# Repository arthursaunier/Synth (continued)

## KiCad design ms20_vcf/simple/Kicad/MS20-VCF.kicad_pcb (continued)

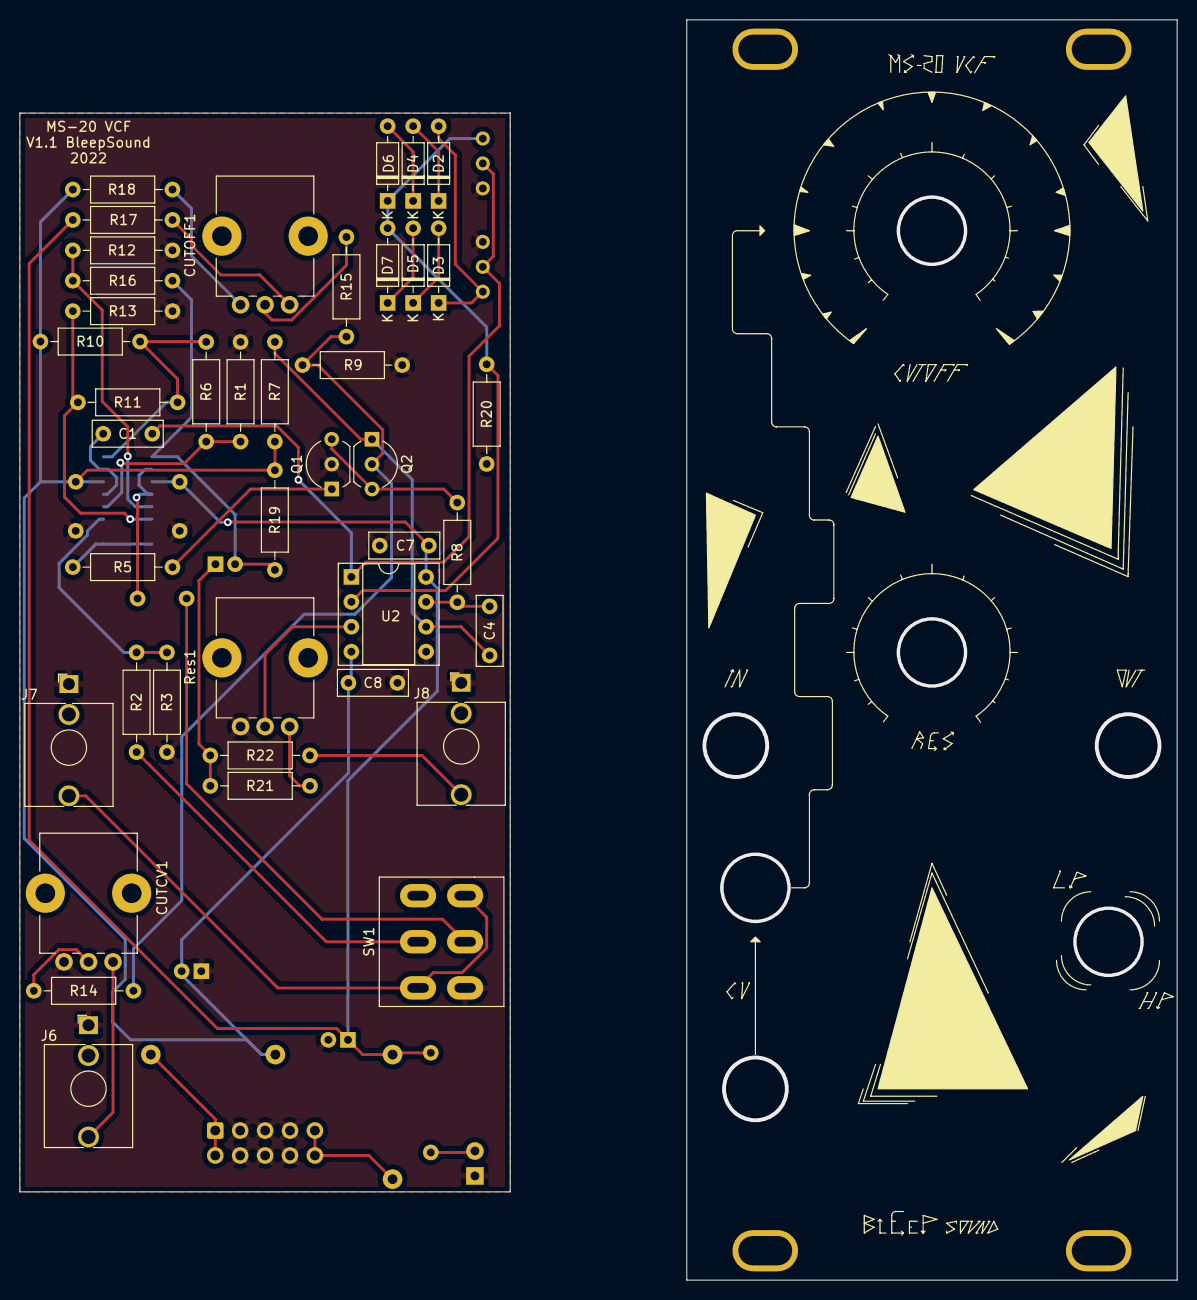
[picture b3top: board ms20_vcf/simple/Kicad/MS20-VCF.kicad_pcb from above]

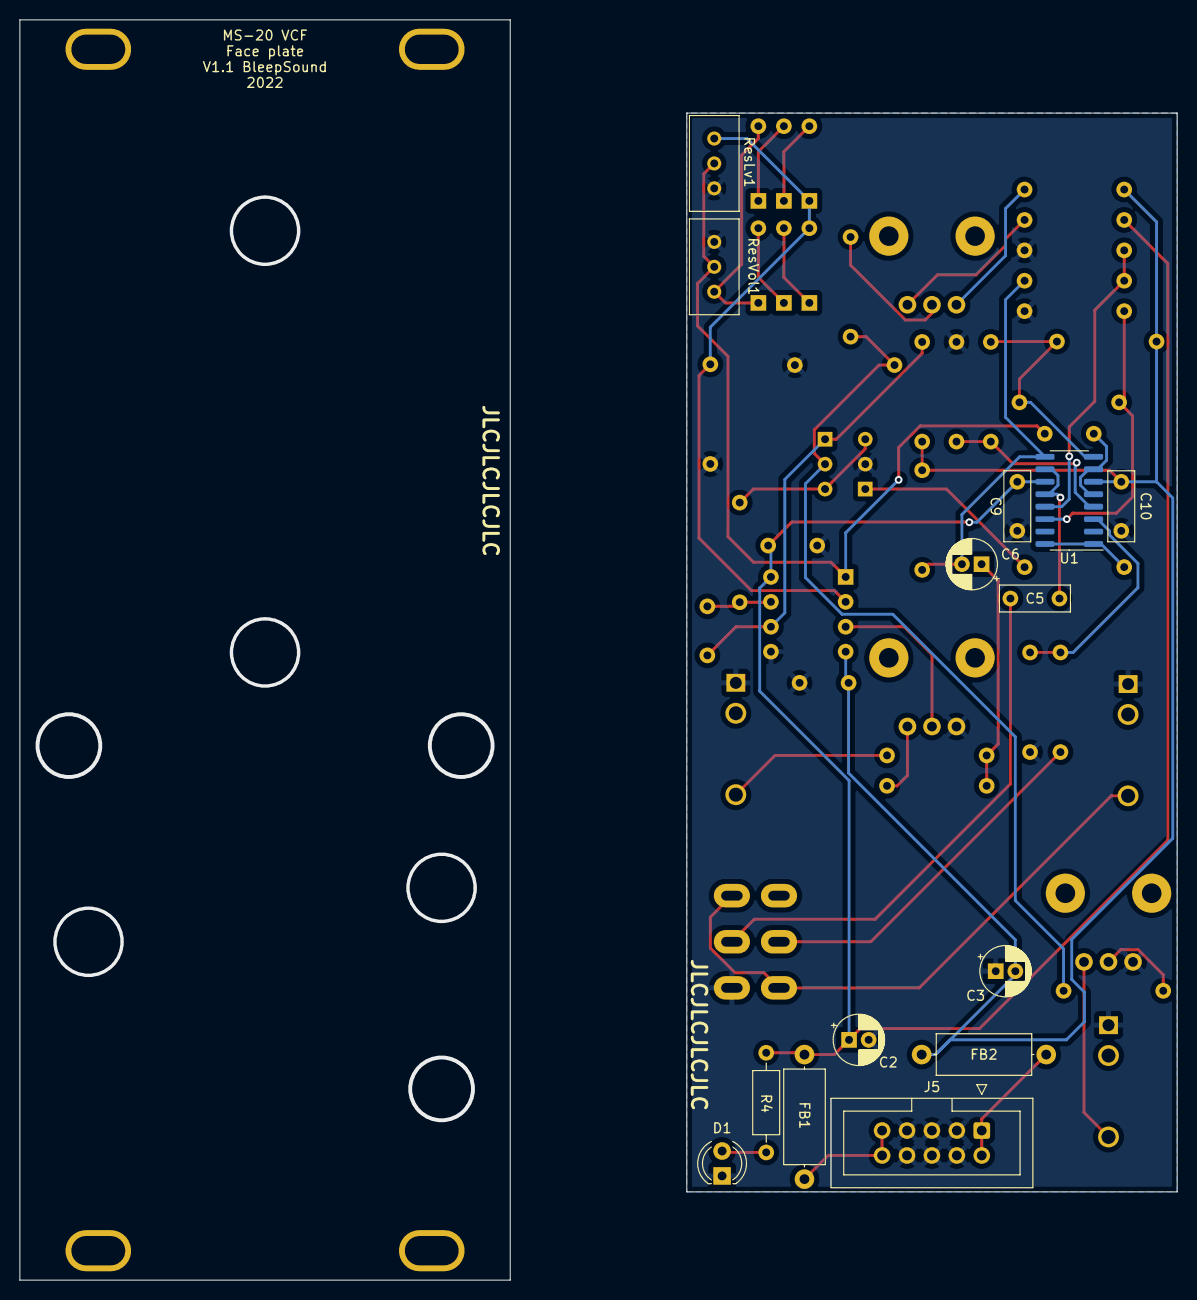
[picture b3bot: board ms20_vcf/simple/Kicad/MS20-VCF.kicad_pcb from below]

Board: 2 copper layers, 118.0 x 128.5 mm, 59 parts (14 on the bottom side), 39 nets.

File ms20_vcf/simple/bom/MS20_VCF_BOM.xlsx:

References | Quantity | Value | Footprint | Specs | Link | Price/100 | Price
C7, C8, C9, C10 | 4 | 100nF | C_Disc_D7.0mm_W2.5mm_P5.00mm | 100nF, 50V, ceramic disc | https://www.taydaelectronics.com/capacitors/ceramic-disc-cap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 | 0.01 | 0.04
C1, C4, C5 | 3 | 1nF | C_Disc_D7.0mm_W2.5mm_P5.00mm | 1nF, 50V, ceramic disc | https://www.taydaelectronics.com/capacitors/ceramic-disc-cap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 | 0.01 | 0.03
C2, C3, C6 | 3 | 10µ | CP_Radial_D5.0mm_P2.00mm | 10µF, 50V | https://www.taydaelectronics.com/capacitors/electrolytic-cap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 | 0.02 | 0.06
FB1, FB2 | 2 | 10R | L_Axial_L9.5mm_D4.0mm_P12.70mm_Horizontal_Fastron_SMCC |  | https://www.taydaelectronics.com/axial-ferrite-bead-76-ohm.html | 0.08 | 0.16
R2, R6, R7, R11, R15, R16 | 6 | 100k | R_Axial_DIN0207_L6.3mm_D2.5mm_P10.16mm_Horizontal | 1/4W metal film 1% resistor | https://www.taydaelectronics.com/resistors/1-4w-metal-film-r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 | 1.4999999999999999E-2 | 0.09
R1, R3, R12, R13 | 4 | 470R | R_Axial_DIN0207_L6.3mm_D2.5mm_P10.16mm_Horizontal | 1/4W metal film 1% resistor | https://www.taydaelectronics.com/resistors/1-4w-metal-film-r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 | 1.4999999999999999E-2 | 0.06
R4, R5, R9, R20 | 4 | 2.2k | R_Axial_DIN0207_L6.3mm_D2.5mm_P10.16mm_Horizontal | 1/4W metal film 1% resistor | https://www.taydaelectronics.com/resistors/1-4w-metal-film-r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 | 1.4999999999999999E-2 | 0.06
R8, R21, R22 | 3 | 1k | R_Axial_DIN0207_L6.3mm_D2.5mm_P10.16mm_Horizontal | 1/4W metal film 1% resistor | https://www.taydaelectronics.com/resistors/1-4w-metal-film-r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 | 1.4999999999999999E-2 | 4.4999999999999998E-2
R10, R19 | 2 | 1.8k | R_Axial_DIN0207_L6.3mm_D2.5mm_P10.16mm_Horizontal | 1/4W metal film 1% resistor | https://www.taydaelectronics.com/resistors/1-4w-metal-film-r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 | 1.4999999999999999E-2 | 0.03
R14 | 1 | 82k | R_Axial_DIN0207_L6.3mm_D2.5mm_P10.16mm_Horizontal | 1/4W metal film 1% resistor | https://www.taydaelectronics.com/resistors/1-4w-metal-film-r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 | 1.4999999999999999E-2 | 1.4999999999999999E-2
R17 | 1 | 33k | R_Axial_DIN0207_L6.3mm_D2.5mm_P10.16mm_Horizontal | 1/4W metal film 1% resistor | https://www.taydaelectronics.com/resistors/1-4w-metal-film-r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 | 1.4999999999999999E-2 | 1.4999999999999999E-2
R18 | 1 | 56k | R_Axial_DIN0207_L6.3mm_D2.5mm_P10.16mm_Horizontal | 1/4W metal film 1% resistor | https://www.taydaelectronics.com/resistors/1-4w-metal-film-r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 | 1.4999999999999999E-2 | 1.4999999999999999E-2
D2, D3, D4, D5, D6, D7 | 6 | 1N4148 | D_DO-35_SOD27_P7.62mm_Horizontal | 1N4148 diode | https://www.taydaelectronics.com/1n4148-switching-signal-diode.html | 0.01 | 0.06
D1 | 1 | LED-12V | LED_D4.0mm |  | https://www.taydaelectronics.com/leds/round-leds/5mm-leds.html | 0.03 | 0.03
U1 | 1 | LM13700 | SOIC-16_3.9x9.9mm_P1.27mm | OTA | https://www.taydaelectronics.com/lm13700-lm13700n-operationa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 | 3.99 | 1.99
U2 | 2 | TL072 | DIP-8_W7.62mm_Socket | OpAmp | https://www.taydaelectronics.com/tl072-low-noise-j-fet-dual-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 | 1.99 | 3.98
SW1 | 1 | Hpass/Lpass Switch | SW_DPDT_Toggle |  | https://www.taydaelectronics.com/mini-toggle-switch-dpdt-on-on.html | 0.59 | 0.59
CUTCV1, CUTOFF1, Res1 | 3 | 100k | Potentiometer_Bourns_PTV09A-1_Single_Vertical |  | https://www.mouser.fr/ProductDetail/652-PTV09A4025FB104 | 0.84699999999999998 | 2.5409999999999999
ResLv1 | 1 | 3.3k | Potentiometer_Bourns_3386C_Horizontal |  | https://www.taydaelectronics.com/10k-ohm-trimmer-potentiomet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 | 0.28000000000000003 | 0.28000000000000003
ResVol1 | 1 | 10k | Potentiometer_Bourns_3386C_Horizontal |  | https://www.taydaelectronics.com/10k-ohm-trimmer-potentiomet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 | 0.28000000000000003 | 0.28000000000000003
Q1, Q2 | 2 | BC559 | TO-92_Inline |  | https://www.taydaelectronics.com/bc559bta-bc559b-bc559-trans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 | 0.08 | 0.16
J5 | 1 | Power Input | IDC-Header_2x05_P2.54mm_Vertical |  | https://www.taydaelectronics.com/10-pin-box-header-connector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 | 0.15 | 0.15
J6, J7, J8 | 3 |  | Jack_3.5mm_QingPu_WQP-PJ398SM_Vertical_CircularHoles | 3,5mm mono Jack socket | https://www.thonk.co.uk/shop/3-5mm-jacks/ | 0.32 | 0.96
 |  |  |  |  |  | Total | 11.600999999999999

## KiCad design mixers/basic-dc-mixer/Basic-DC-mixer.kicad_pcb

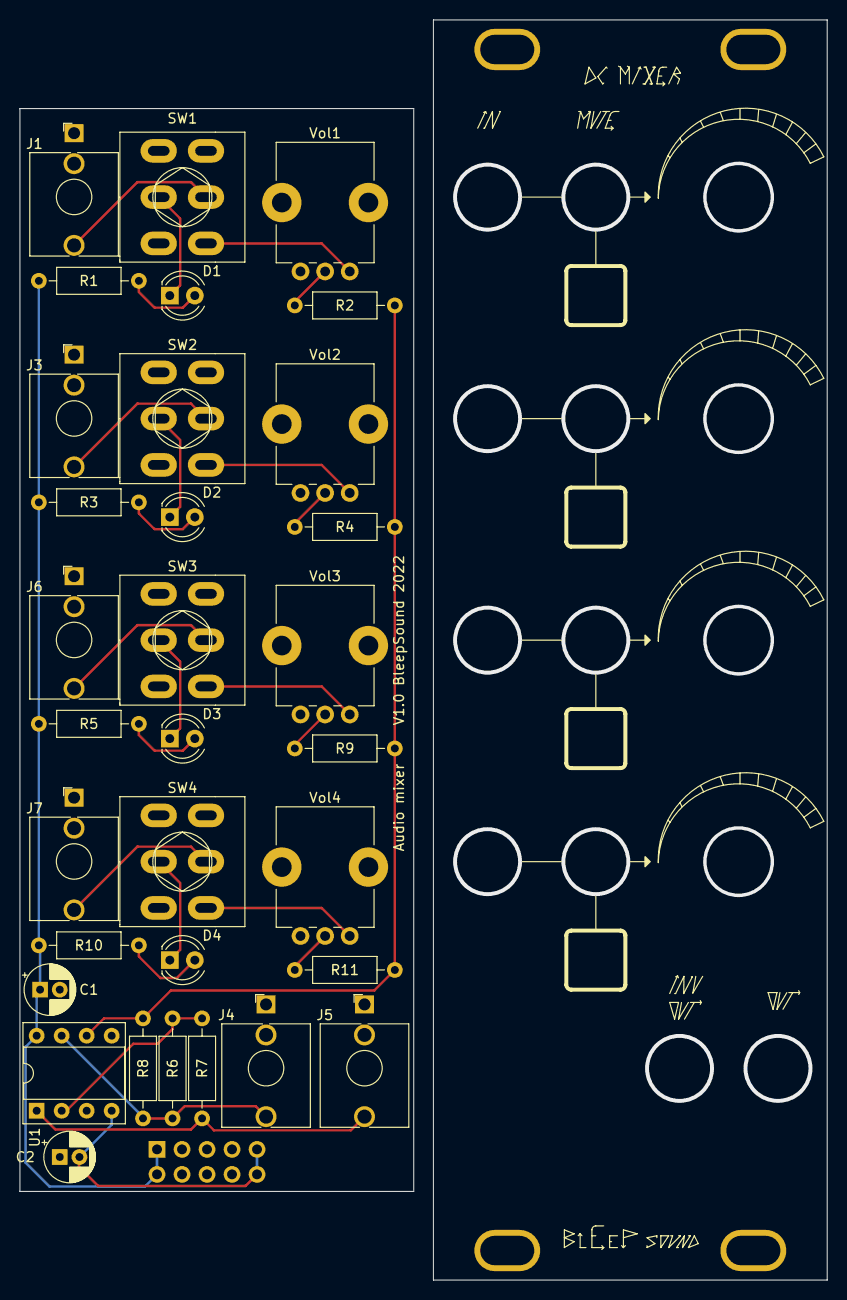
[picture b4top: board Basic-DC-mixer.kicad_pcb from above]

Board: 2 copper layers, 82.0 x 128.0 mm, 37 parts (1 on the bottom side), 27 nets.

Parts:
C1, C2: 10µ; CP_Radial_D5.0mm_P2.00mm
D1, D2, D3, D4: LED-mute; LED_D4.0mm
H1, H2, H3, H4: MountingHole; Doepfer Mounting hole
J1, J3, J6, J7: In; Thonkiconn
J2: Power Input; PinHeader_2x05_P2.54mm_Vertical
J4: InvOut; Thonkiconn
J5: Out; Thonkiconn
R1, R3, R5, R10: 4.7k; R_Axial_DIN0207_L6.3mm_D2.5mm_P10.16mm_Horizontal
R2, R4, R8, R9, R11: 100k; R_Axial_DIN0207_L6.3mm_D2.5mm_P10.16mm_Horizontal
R6, R7: 10k; R_Axial_DIN0207_L6.3mm_D2.5mm_P10.16mm_Horizontal
SW1, SW2, SW3, SW4: Mute; SW_DPDT_Toggle
U1: TL072; DIP-8_W7.62mm_Socket
Vol1, Vol2, Vol3, Vol4: 10k; Pot-bourns-alpha

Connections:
+12V: C1.1, J2.1, J2.2, R1.1, R3.1, R5.1, R10.1, U1.8 (V+)
-12V: C2.2, J2.9, J2.10, U1.4 (V-)
GND: C1.2, C2.1, J1.S, J2.3, J2.4, J2.5, J2.6, J2.7, J2.8, J3.S, J4.S, J5.S, J6.S, J7.S, SW1.1 (A), SW2.1 (A), SW3.1 (A), SW4.1 (A), U1.3 (+), U1.5 (+), Vol1.3, Vol2.3, Vol3.3, Vol4.3
unnamed: D1.1 (K), SW1.2 (B)
unnamed: D1.2 (A), R1.2
unnamed: D2.1 (K), SW2.2 (B)
unnamed: D2.2 (A), R3.2
unnamed: D3.1 (K), SW3.2 (B)
unnamed: D3.2 (A), R5.2
unnamed: D4.1 (K), SW4.2 (B)
unnamed: D4.2 (A), R10.2
unnamed: J1.T, SW1.5 (B)
unnamed: J3.T, SW2.5 (B)
unnamed: J4.T, R6.2, R8.1, U1.7
unnamed: J5.T, R7.1, U1.1
unnamed: J6.T, SW3.5 (B)
unnamed: J7.T, SW4.5 (B)
unnamed: R2.2, Vol1.2
unnamed: R4.2, Vol2.2
unnamed: R6.1, R7.2, U1.2 (-)
unnamed: R9.2, Vol3.2
unnamed: R2.1, R4.1, R8.2, R9.1, R11.1, U1.6 (-)
unnamed: R11.2, Vol4.2
unnamed: SW1.6 (C), Vol1.1
unnamed: SW2.6 (C), Vol2.1
unnamed: SW3.6 (C), Vol3.1
unnamed: SW4.6 (C), Vol4.1

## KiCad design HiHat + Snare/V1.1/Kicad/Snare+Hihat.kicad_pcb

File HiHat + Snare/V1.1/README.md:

# Hi-Hat + Snare

## V1.1

2 white noise generators with VCAs to create Hihat or Snare sound. 

Built on the same module, with 2 separate voices (completly independent)

No CV

This version adds boxed IDC headers, minor corrections on components positions and a gain change of the output buffers on each voice.

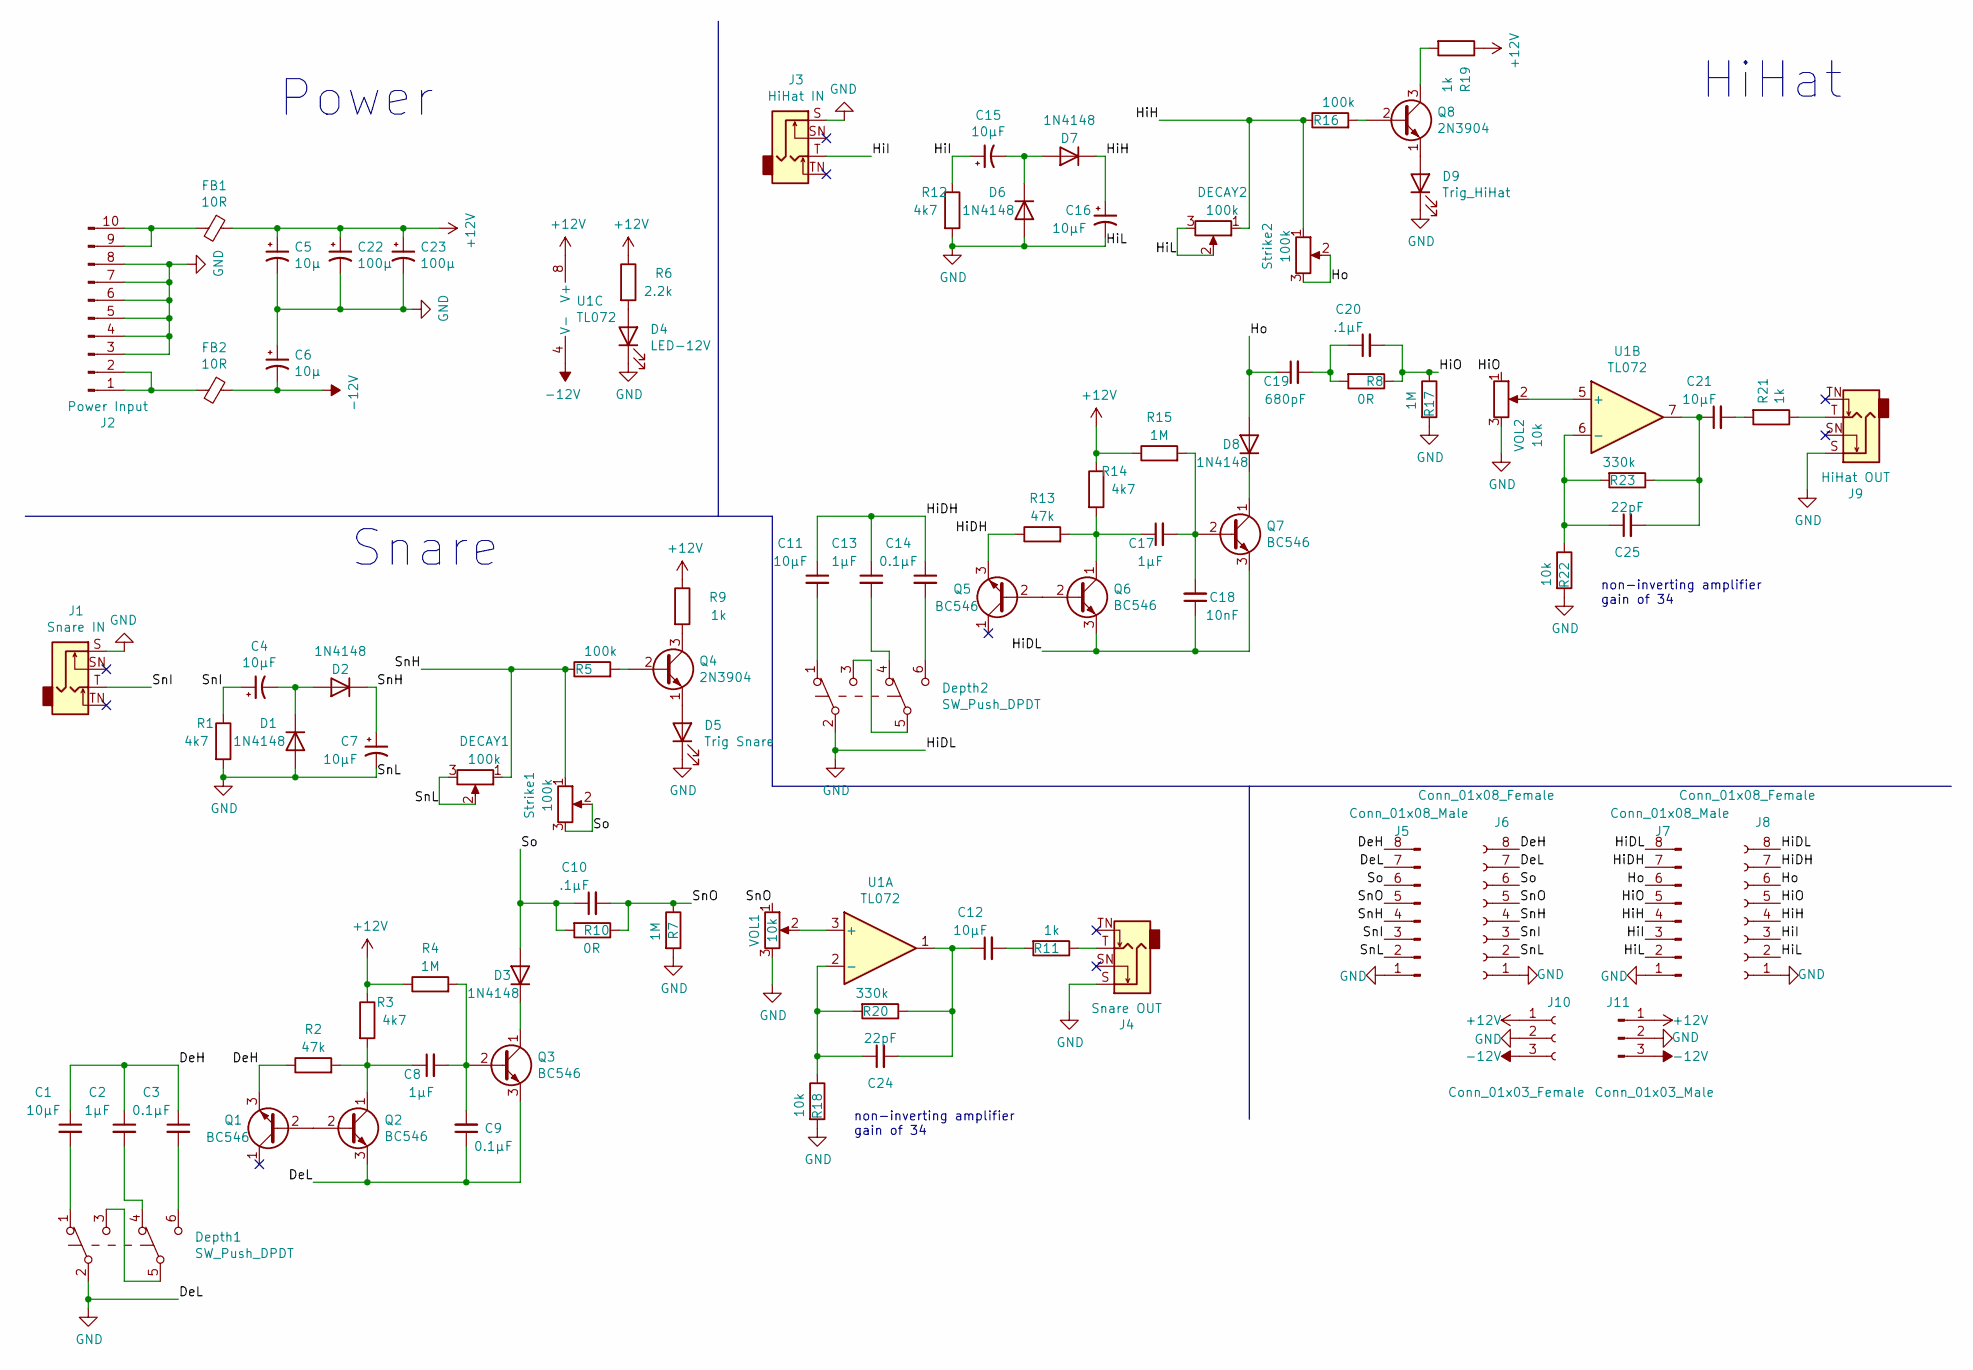
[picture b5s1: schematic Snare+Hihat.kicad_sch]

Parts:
C1, C11, C12, C21: 10µF; C_Disc_D7.0mm_W2.5mm_P5.00mm
C2, C8, C13, C17: 1µF; C_Disc_D7.0mm_W2.5mm_P5.00mm
C3, C9, C14: 0.1µF; C_Disc_D7.0mm_W2.5mm_P5.00mm
C4, C7, C15, C16: 10µF; CP_Radial_D5.0mm_P2.00mm
C5, C6: 10µ; CP_Radial_D5.0mm_P2.00mm
C10, C20: .1µF; C_Disc_D7.0mm_W2.5mm_P5.00mm
C18: 10nF; C_Disc_D7.0mm_W2.5mm_P5.00mm
C19: 680pF; C_Disc_D7.0mm_W2.5mm_P5.00mm
C22, C23: 100µ; CP_Radial_D5.0mm_P2.00mm
C24, C25: 22pF; C_Disc_D7.0mm_W2.5mm_P5.00mm
D1, D2, D3, D6, D7, D8: 1N4148; D_DO-35_SOD27_P7.62mm_Horizontal
D4: LED-12V; LED_D4.0mm
D5: Trig Snare; LED_D4.0mm
D9: Trig_HiHat; LED_D4.0mm
DECAY1, DECAY2: 100k; Pot-bourns-alpha
Depth1, Depth2: SW_Push_DPDT; SW_DPDT_Toggle
FB1, FB2: 10R; L_Axial_L9.5mm_D4.0mm_P12.70mm_Horizontal_Fastron_SMCC
J1: Snare IN; Thonkiconn
J2: Power Input; IDC-Header_2x05_P2.54mm_Vertical
J3: HiHat IN; Thonkiconn
J4: Snare OUT; Thonkiconn
J5, J7: Conn_01x08_Male; PinHeader_1x08_P2.54mm_Vertical
J6, J8: Conn_01x08_Female; PinSocket_1x08_P2.54mm_Vertical
J9: HiHat OUT; Thonkiconn
J10: Conn_01x03_Female; PinSocket_1x03_P2.54mm_Vertical
J11: Conn_01x03_Male; PinHeader_1x03_P2.54mm_Vertical
Q1, Q2, Q3, Q5, Q6, Q7: BC546; TO-92_Inline
Q4, Q8: 2N3904; TO-92_Inline
R1, R3, R12, R14: 4k7; R_Axial_DIN0207_L6.3mm_D2.5mm_P10.16mm_Horizontal
R2, R13: 47k; R_Axial_DIN0207_L6.3mm_D2.5mm_P10.16mm_Horizontal
R4, R7, R15, R17: 1M; R_Axial_DIN0207_L6.3mm_D2.5mm_P10.16mm_Horizontal
R5, R16: 100k; R_Axial_DIN0207_L6.3mm_D2.5mm_P2.54mm_Vertical
R6: 2.2k; R_Axial_DIN0207_L6.3mm_D2.5mm_P10.16mm_Horizontal
R8, R10: 0R; R_Axial_DIN0207_L6.3mm_D2.5mm_P10.16mm_Horizontal
R9, R19: 1k; R_Axial_DIN0207_L6.3mm_D2.5mm_P2.54mm_Vertical
R11, R21: 1k; R_Axial_DIN0207_L6.3mm_D2.5mm_P10.16mm_Horizontal
R18, R22: 10k; R_Axial_DIN0207_L6.3mm_D2.5mm_P2.54mm_Vertical
R20, R23: 330k; R_Axial_DIN0207_L6.3mm_D2.5mm_P2.54mm_Vertical
Strike1, Strike2: 100k; Pot-bourns-alpha
U1: TL072; DIP-8_W7.62mm_Socket
VOL1, VOL2: 10k; Pot-bourns-alpha

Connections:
+12V: C5.1, C22.1, C23.1, FB1.1, J10.1, J11.1, R3.1, R4.1, R6.1, R9.1, R14.1, R15.1, R19.1, U1.8 (V+)
-12V: C6.2, FB2.1, J10.3, J11.3, U1.4 (V-)
/DeH: C1.1, C2.1, C3.1, J5.8, J6.8, Q1.3 (E), R2.1
/HiDH: C11.1, C13.1, C14.1, J7.7, J8.7, Q5.3 (E), R13.1
/HiH: C16.1, D7.1 (K), DECAY2.1, J7.4, J8.4, R16.1, Strike2.1
/HiI: C15.1, J3.T, J7.3, J8.3, R12.1
/HiO: C20.2, J7.5, J8.5, R8.1, R17.1, VOL2.1
/Ho: C19.1, D8.2 (A), J7.6, J8.6, Strike2.2, Strike2.3
/SnH: C7.1, D2.1 (K), DECAY1.1, J5.4, J6.4, R5.1, Strike1.1
/SnI: C4.1, J1.T, J5.3, J6.3, R1.1
/SnO: C10.2, J5.5, J6.5, R7.1, R10.1, VOL1.1
/So: C10.1, D3.2 (A), J5.6, J6.6, R10.2, Strike1.2, Strike1.3
GND: C5.2, C6.1, C7.2, C9.1, C16.2, C18.1, C22.2, C23.2, D1.2 (A), D4.1 (K), D5.1 (K), D6.2 (A), D9.1 (K), DECAY1.2, DECAY1.3, DECAY2.2, DECAY2.3, Depth1.2 (B), Depth2.2 (B), J1.S, J2.3, J2.4, J2.5, J2.6, J2.7, J2.8, J3.S, J4.S, J5.1, J5.2, J5.7, J6.1, J6.2, J6.7, J7.1, J7.2, J7.8, J8.1, J8.2, J8.8, J9.S, J10.2, J11.2, Q2.3 (E), Q3.3 (E), Q6.3 (E), Q7.3 (E), R1.2, R7.2, R12.2, R17.2, R18.2, R22.2, VOL1.3, VOL2.3
unnamed: C1.2, Depth1.1 (A)
unnamed: C2.2, Depth1.4 (A)
unnamed: C3.2, Depth1.6 (C)
unnamed: C4.2, D1.1 (K), D2.2 (A)
unnamed: C8.1, Q2.1 (C), R2.2, R3.2
unnamed: C8.2, C9.2, Q3.2 (B), R4.2
unnamed: C11.2, Depth2.1 (A)
unnamed: C12.1, C24.2, R20.1, U1.1
unnamed: C12.2, R11.2
unnamed: C13.2, Depth2.4 (A)
unnamed: C14.2, Depth2.6 (C)
unnamed: C15.2, D6.1 (K), D7.2 (A)
unnamed: C17.1, Q6.1 (C), R13.2, R14.2
unnamed: C17.2, C18.2, Q7.2 (B), R15.2
unnamed: C19.2, C20.1, R8.2
unnamed: C21.1, C25.2, R23.1, U1.7
unnamed: C21.2, R21.2
unnamed: D3.1 (K), Q3.1 (C)
unnamed: D4.2 (A), R6.2
unnamed: D5.2 (A), Q4.1 (E)
unnamed: D8.1 (K), Q7.1 (C)
unnamed: D9.2 (A), Q8.1 (E)
unnamed: Depth1.3 (C), Depth1.5 (B)
unnamed: Depth2.3 (C), Depth2.5 (B)
unnamed: FB1.2, J2.9, J2.10
unnamed: FB2.2, J2.1, J2.2
unnamed: J4.T, R11.1
unnamed: J9.T, R21.1
unnamed: Q1.2 (B), Q2.2 (B)
unnamed: Q4.2 (B), R5.2
unnamed: Q4.3 (C), R9.2
unnamed: Q5.2 (B), Q6.2 (B)
unnamed: Q8.2 (B), R16.2
unnamed: Q8.3 (C), R19.2
unnamed: C24.1, R18.1, R20.2, U1.2 (-)
unnamed: U1.3 (+), VOL1.2
unnamed: U1.5 (+), VOL2.2
unnamed: C25.1, R22.1, R23.2, U1.6 (-)

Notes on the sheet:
Snare
non-inverting amplifier gain of 34
Power
HiHat

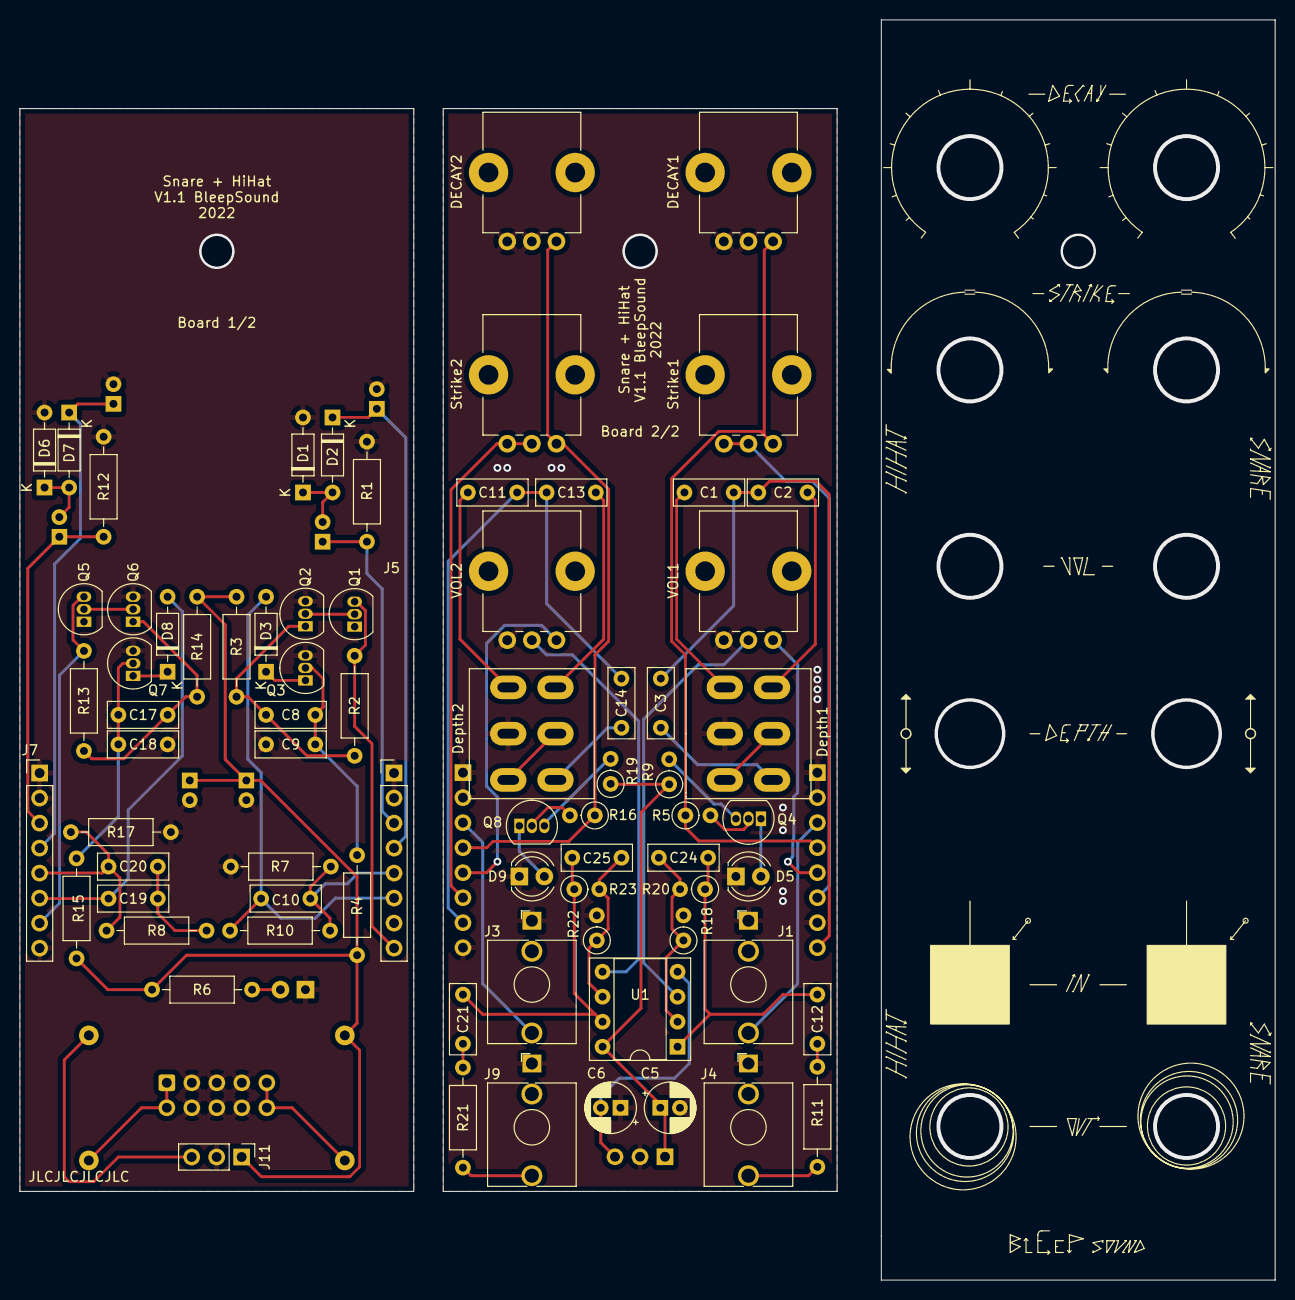
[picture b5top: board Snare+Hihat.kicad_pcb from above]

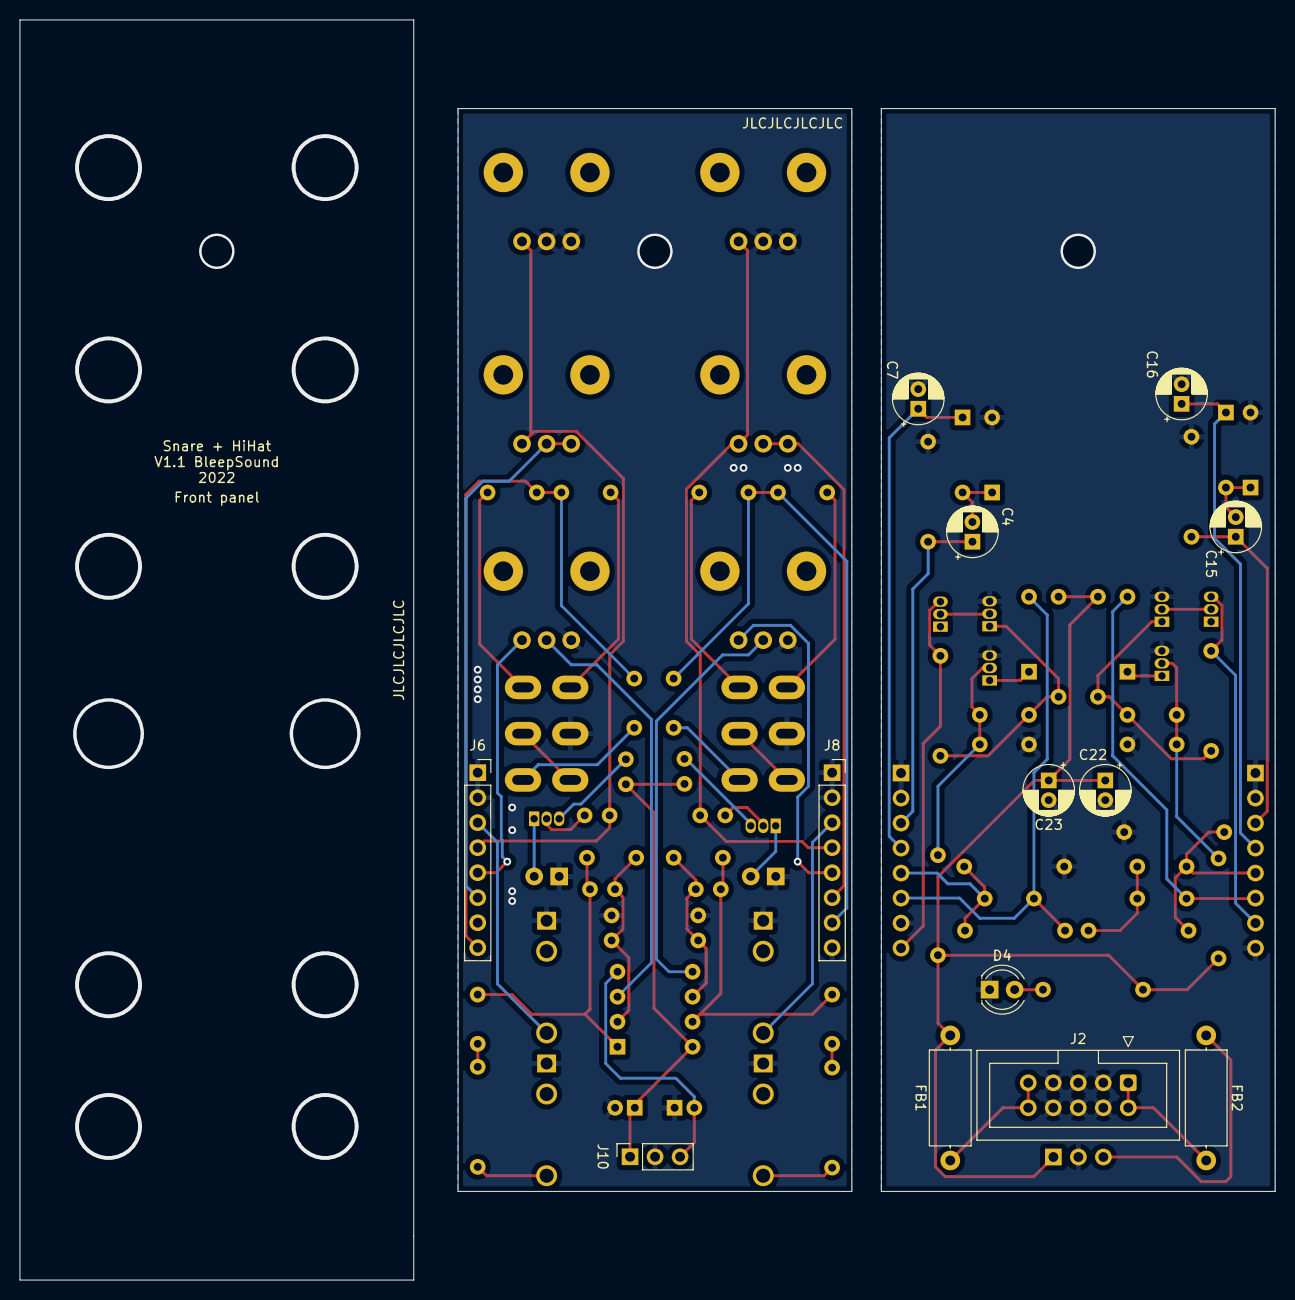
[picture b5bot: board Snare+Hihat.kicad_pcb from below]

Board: 2 copper layers, 127.5 x 128.0 mm, 87 parts (13 on the bottom side), 51 nets.

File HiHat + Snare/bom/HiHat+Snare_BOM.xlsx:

References | Quantity | Value | Footprint | Specs | Link | Price/100 | Price
C3, C9, C10, C14, C20 | 5 | 0,1µF | C_Disc_D7.0mm_W2.5mm_P5.00mm | 0,1µF, 50V, ceramic disc | https://www.taydaelectronics.com/capacitors/ceramic-disc-cap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 | 0.01 | 0.05
C4, C5, C6, C7, C15, C16 | 6 | 10µ | CP_Radial_D5.0mm_P2.00mm | 10µF, 50V | https://www.taydaelectronics.com/capacitors/electrolytic-cap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 | 0.02 | 0.12
C1, C11, C12, C21 | 4 | 10µF | C_Disc_D7.0mm_W2.5mm_P5.00mm | 10µF, 50V, ceramic disc | https://www.taydaelectronics.com/capacitors/ceramic-disc-cap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 | 0.01 | 0.04
C2, C8, C13, C17 | 4 | 1µF | C_Disc_D7.0mm_W2.5mm_P5.00mm | 1µF, 50V, ceramic disc | https://www.taydaelectronics.com/capacitors/ceramic-disc-cap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 | 0.01 | 0.04
C18 | 1 | 10nF | C_Disc_D7.0mm_W2.5mm_P5.00mm | 10nF, 50V, ceramic disc | https://www.taydaelectronics.com/capacitors/ceramic-disc-cap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 | 0.01 | 0.01
C19 | 1 | 680pF | C_Disc_D7.0mm_W2.5mm_P5.00mm | 680pF, 50V, ceramic disc | https://www.taydaelectronics.com/capacitors/ceramic-disc-cap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 | 0.01 | 0.01
C22, C23 | 2 | 100µ | CP_Radial_D5.0mm_P2.00mm | 100µF, 25V | https://www.taydaelectronics.com/capacitors/electrolytic-cap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 | 0.03 | 0.06
FB1, FB2 | 2 | 10R | L_Axial_L9.5mm_D4.0mm_P12.70mm_Horizontal_Fastron_SMCC |  | https://www.taydaelectronics.com/axial-ferrite-bead-76-ohm.html | 0.08 | 0.16
R1, R3, R12, R14 | 4 | 4,7k | R_Axial_DIN0207_L6.3mm_D2.5mm_P10.16mm_Horizontal | 1/4W metal film 1% resistor | https://www.taydaelectronics.com/resistors/1-4w-metal-film-r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 | 1.4999999999999999E-2 | 0.06
R4, R7, R15, R17 | 4 | 1M | R_Axial_DIN0207_L6.3mm_D2.5mm_P10.16mm_Horizontal | 1/4W metal film 1% resistor | https://www.taydaelectronics.com/resistors/1-4w-metal-film-r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 | 1.4999999999999999E-2 | 0.06
R9, R11, R19, R21 | 4 | 1k | R_Axial_DIN0207_L6.3mm_D2.5mm_P10.16mm_Horizontal | 1/4W metal film 1% resistor | https://www.taydaelectronics.com/resistors/1-4w-metal-film-r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 | 1.4999999999999999E-2 | 0.06
R2, R13 | 2 | 47k | R_Axial_DIN0207_L6.3mm_D2.5mm_P10.16mm_Horizontal | 1/4W metal film 1% resistor | https://www.taydaelectronics.com/resistors/1-4w-metal-film-r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 | 1.4999999999999999E-2 | 0.03
R5, R16 | 2 | 100k | R_Axial_DIN0207_L6.3mm_D2.5mm_P10.16mm_Horizontal | 1/4W metal film 1% resistor | https://www.taydaelectronics.com/resistors/1-4w-metal-film-r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 | 1.4999999999999999E-2 | 0.03
R8, R10 | 2 | 0R | R_Axial_DIN0207_L6.3mm_D2.5mm_P10.16mm_Horizontal | DNP | https://www.taydaelectronics.com/resistors/1-4w-metal-film-r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 | 1.4999999999999999E-2 | 0.03 | DNP
R6 | 1 | 2,2K | R_Axial_DIN0207_L6.3mm_D2.5mm_P10.16mm_Horizontal | 1/4W metal film 1% resistor | https://www.taydaelectronics.com/resistors/1-4w-metal-film-r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 | 1.4999999999999999E-2 | 1.4999999999999999E-2
D1, D2, D3, D6, D7, D8 | 6 | 1N4148 | D_DO-35_SOD27_P7.62mm_Horizontal | 1N4148 diode | https://www.taydaelectronics.com/1n4148-switching-signal-diode.html | 0.01 | 0.06
D4, D5, D9 | 3 | LED | LED_D4.0mm |  | https://www.taydaelectronics.com/leds/round-leds/5mm-leds.html | 0.03 | 0.09
U1 | 1 | TL072 | DIP-8_W7.62mm_Socket | OpAmp | https://www.taydaelectronics.com/tl072-low-noise-j-fet-dual-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 | 1.99 | 1.99
Depth1, Depth2 | 2 | Depth Switch | SW_DPDT_Toggle |  | https://www.taydaelectronics.com/mini-toggle-switch-dpdt-on-on.html | 0.59 | 1.18
DECAY1, DECAY2, Strike1, Strike2 | 4 | 100k | Potentiometer_Bourns_PTV09A-1_Single_Vertical |  | https://www.mouser.fr/ProductDetail/652-PTV09A4025FB104 | 0.84699999999999998 | 3.3879999999999999
VOL1, VOL2 | 2 | 10k | Potentiometer_Bourns_PTV09A-1_Single_Vertical |  | https://www.mouser.fr/ProductDetail/652-PTV09A4025FB104 | 0.84699999999999998 | 1.694
Q1, Q2, Q3, Q5, Q6, Q7 | 6 | BC546 | TO-92_Inline |  | https://www.taydaelectronics.com/bc546-transistor-npn-65v-0-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 | 0.03 | 0.18
Q4, Q8 | 2 | 2N3904 | TO-92_Inline |  | https://www.taydaelectronics.com/2n3904-npn-general-propose-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 | 0.02 | 0.04
J5, J7 | 2 | Conn_01x08_Male | PinHeader_1x08_P2.54mm_Vertical |  | https://www.taydaelectronics.com/40-pin-2-54-mm-single-row-p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 | 3.7499999999999999E-2 | 7.4999999999999997E-2
J6, J8 | 2 | Conn_01x08_Female | PinSocket_1x08_P2.54mm_Vertical |  | https://www.taydaelectronics.com/40-pin-2-54-mm-single-row-f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 | 0.05 | 0.1
J10 | 1 | Conn_01x03_Female | PinSocket_1x03_P2.54mm_Vertical |  | https://www.taydaelectronics.com/40-pin-2-54-mm-single-row-f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 | 0.05 | 0.05
J11 | 1 | Conn_01x03_Male | PinHeader_1x03_P2.54mm_Vertical |  | https://www.taydaelectronics.com/40-pin-2-54-mm-single-row-p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 | 3.7499999999999999E-2 | 3.7499999999999999E-2
J2 | 1 | Power Input | PinHeader_2x05_P2.54mm_Vertical |  | https://www.taydaelectronics.com/2x40-pin-2-54-mm-double-row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 | 0.05 | 0.05
J1, J3, J4, J9 | 4 |  | Jack_3.5mm_QingPu_WQP-PJ398SM_Vertical_CircularHoles | 3,5mm mono Jack socket | https://www.thonk.co.uk/shop/3-5mm-jacks/ | 0.32 | 1.28
 |  |  |  |  |  | Total | 10.989499999999998

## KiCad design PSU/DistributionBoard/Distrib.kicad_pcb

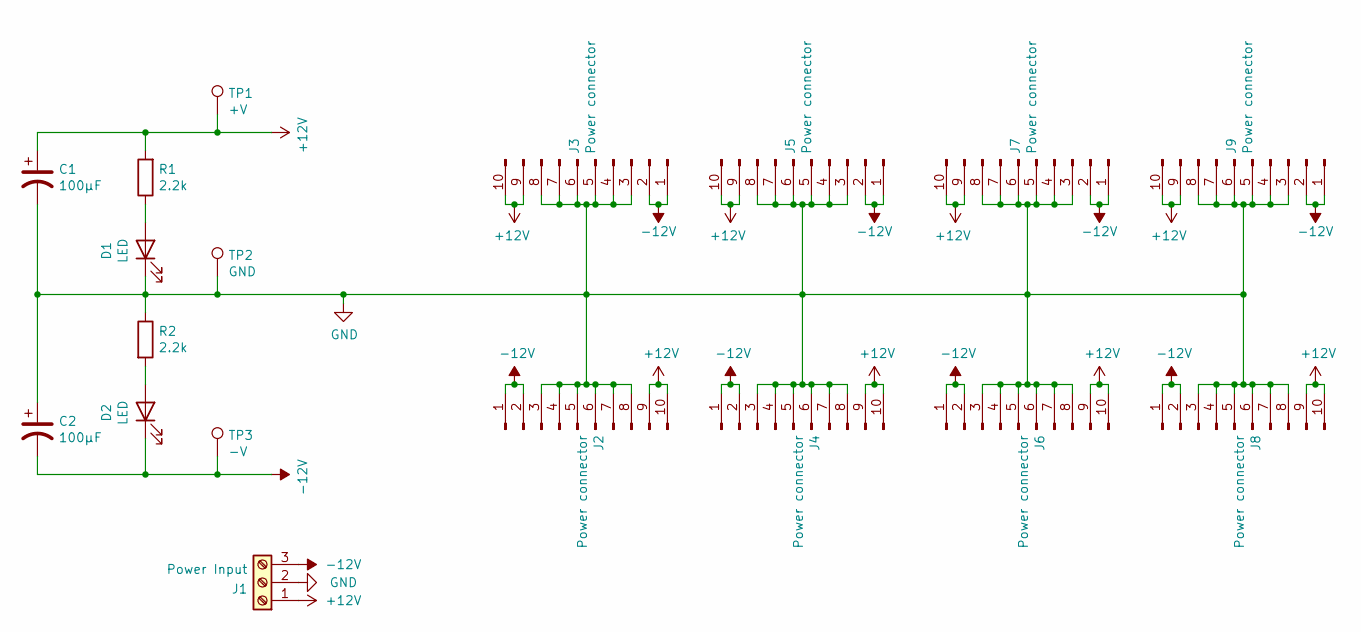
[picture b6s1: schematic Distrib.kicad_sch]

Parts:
C1, C2: 100µF; CP_Radial_D5.0mm_P2.00mm
D1, D2: LED; LED_D5.0mm_Clear
J1: Power Input; TerminalBlock_bornier-3_P5.08mm
J2, J3, J4, J5, J6, J7, J8, J9: Power connector; PinHeader_2x05_P2.54mm_Vertical
R1, R2: 2.2k; R_Axial_DIN0309_L9.0mm_D3.2mm_P12.70mm_Horizontal
TP1: +V; TestPoint_Keystone_5000-5004_Miniature
TP2: GND; TestPoint_Keystone_5000-5004_Miniature
TP3: -V; TestPoint_Keystone_5000-5004_Miniature

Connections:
+12V: C1.1, J1.1, J2.9, J2.10, J3.9, J3.10, J4.9, J4.10, J5.9, J5.10, J6.9, J6.10, J7.9, J7.10, J8.9, J8.10, J9.9, J9.10, R1.2, TP1.1; also elsewhere on the board
-12V: C2.2, D2.1 (K), J1.3, J2.1, J2.2, J3.1, J3.2, J4.1, J4.2, J5.1, J5.2, J6.1, J6.2, J7.1, J7.2, J8.1, J8.2, J9.1, J9.2, TP3.1; also elsewhere on the board
GND: C1.2, C2.1, D1.1 (K), J1.2, J2.3, J2.4, J2.5, J2.6, J2.7, J2.8, J3.3, J3.4, J3.5, J3.6, J3.7, J3.8, J4.3, J4.4, J4.5, J4.6, J4.7, J4.8, J5.3, J5.4, J5.5, J5.6, J5.7, J5.8, J6.3, J6.4, J6.5, J6.6, J6.7, J6.8, J7.3, J7.4, J7.5, J7.6, J7.7, J7.8, J8.3, J8.4, J8.5, J8.6, J8.7, J8.8, J9.3, J9.4, J9.5, J9.6, J9.7, J9.8, R2.1, TP2.1; also elsewhere on the board
unnamed: D1.2 (A), R1.1
unnamed: D2.2 (A), R2.2

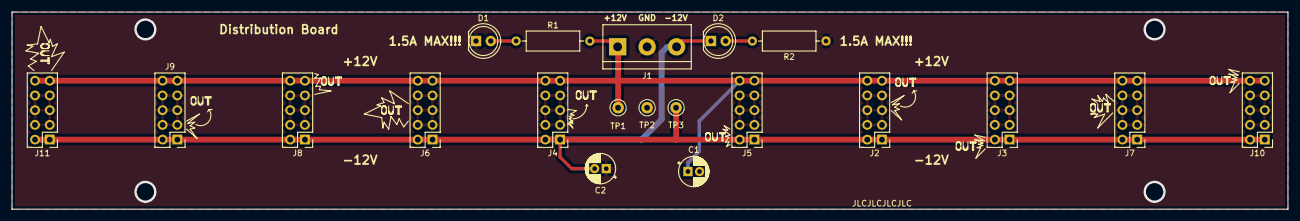
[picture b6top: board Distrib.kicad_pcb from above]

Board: 2 copper layers, 220.0 x 34.0 mm, 20 parts (0 on the bottom side), 5 nets.

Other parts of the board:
J10, J11: Power connector; PinHeader_2x05_P2.54mm_Vertical

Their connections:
+12V: J10.9, J10.10, J11.9, J11.10; also elsewhere on the board
-12V: J10.1, J10.2, J11.1, J11.2; also elsewhere on the board
GND: J10.3, J10.4, J10.5, J10.6, J10.7, J10.8, J11.3, J11.4, J11.5, J11.6, J11.7, J11.8; also elsewhere on the board
